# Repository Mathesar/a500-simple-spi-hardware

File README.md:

# a500-simple-spi-hardware
Simple SPI controller for the Amiga 500 with support for SD-cards and Ethernet controller. Tested on a rev. 5 Amiga 500. It might also work on other revisions and Amiga models but that has not been tested. The design is licensed under CERN OHL-S V2.0
This repository contains the hardware CAD files. For drivers look [here](https://github.com/Mathesar/a500-simple-spi-drivers).
This SPI controller is designed to be as simple as possible so that anyone can build it, hence the "simple" SPI controller.
The design uses no programmable logic chips but only jellybean 3.3V 74LVCXX logic chips and a jellybean quad analog switch.
To make it so simple compromises had to be made. The design therefore does not contain any shifting logic. This is a "bitbanging" design that can only receive or send 1 bit at a time. All the shifting is thus done by the driver software. It is not at bad as it seems though as the driver does not need to generate the SCLK signal.
The SCLK signal is generated automatically by the hardware whenever a bit is read or written. Therefore, using some optimised assembly, this controller can do about 60Kbytes/sec of raw throughput on a plain Amiga 500 with no FAST ram.

It seems I often need ~~3~~ 4 revisions to get things right :-). 

## Revision 1.0
Revision 1.0 was my first attempt. It used a 74HCT688 as the address decoder and did not set MOSI high on reads.
Therefore this version had problems with SD-cards. I fixed it by using A7 instead of D7 to write but this made writes very slow.
Also, the '688 is currently unobtainium. It seems that only simple logic chips like the '00 or '02 are available in all logic families.

## Revision 1.1
So, revision 1.1 was created that solved all above issues. This is the version you can see on the pictures. It no longer uses the 74HCT688 but a combination of OR, NOR and NAND gates.
However, even 1.1 had some minor issues. Firstly I made a small mistake in the address decoder. That one was very easy to patch though and after the patch everything functions as designed. Secondly however, the PCB was slightly too large at the top left corner causing the metal shield to no longer fit. (tested on a revision 5 Amiga 500)

## Revision 1.2
Therefore, revision 1.2 was created that fixes those final issues. I did not built it but it is basically revision 1.1 wwith a slightly resized PCB and the address decoder bug fixed. See [here](https://github.com/Mathesar/a500-simple-spi-hardware/tree/40606e6f381aa33d11fc7373534e6168bc126c18) for all the files for this rev 1.2.

**UPDATE 5-12-2022:**
The setup time on MOSI is marginal during reads. This is because of the ~DECODE signal feeding into U7A. To fix this, pin 2 of U7 should be lifted from the PCB so that it longer makes contact with the pad. This pin should then be connected to pin 3 of U7. On my system the hardware actually worked without the modification but some SD cards can get unreliable if this mod is not done

## Revision 1.3
This is the latest revision incorporating the MOSI setup fix. This version has been built and verified.

## Building hints:
This SPI controller is intended to give an Amiga 500 an SD-card (to be used as a harddisk) and ethernet connectivity. 
The ethernet module is optional and connected via a pinheader and some dupont jumper cables. The SD-card module is definately not optional and soldered directly to the interface as can be seen on the pictures. The reason for this is that the SD-card module supplies 3.3V to the logic chips (and to the optional ethernet controller) via it's onboard voltage regulator.
Pictures of the modules I used are in the schematic and in this repository. It is very important to use exactly the SD-card module as I used. 

The circuit depends on the pinout and the onboard voltage regulator. The circuit also contain an old-fashioned electrolytic capacitor on the +3.3V rail. This component is also mandatory! Without it the voltage regulator on the SD-card module might become unstable.
The pinheader for the SD-card actvity LED and the ethernet module should be right angle types or straight angle types bend over. Otherwise the whole setup becomes too high when the dupont cables are mounted. With right angle pins everything fits nicely under the metal shield.
The pinheader that connects the controller to the 68000 socket on the A500 main board should be "turned" types with round pins. The thin part plugs into the Amiga, the thicker part is soldered on the SPI controller. This is very important as the wrong pins might damage your 68000 socket.
The ethernet module does not really fit internally to the Amiga 500. I have used some long dupont cables that go through to the side expansion slot and the ethernet module is thus hanging outside. Maybe I build something like [this](https://www.thingiverse.com/thing:4830638) someday.

## HDD led
I hotglued a LED to the normal floppy LED and connected that to the LED pins on the simple SPI controller. A bit like done [here](https://www.youtube.com/watch?v=9V46ZEBu338) except that I used a single orange LED. Hotglue is easily removed with some IPA (isopropyl alcohol) if I ever change my mind. It looks really good:

## Compatiblity with other hardware
The simple SPI hardware uses a fixed address space in the upper region of the ZORRO-II IO space. Additional hardware like the A590 side-car should end up in the lower region of the ZORRO-II IO space so in theory they should not interfere. This is untested though.

A picture from the front of revision 1.1:

And a picture from the back of revision 1.1:

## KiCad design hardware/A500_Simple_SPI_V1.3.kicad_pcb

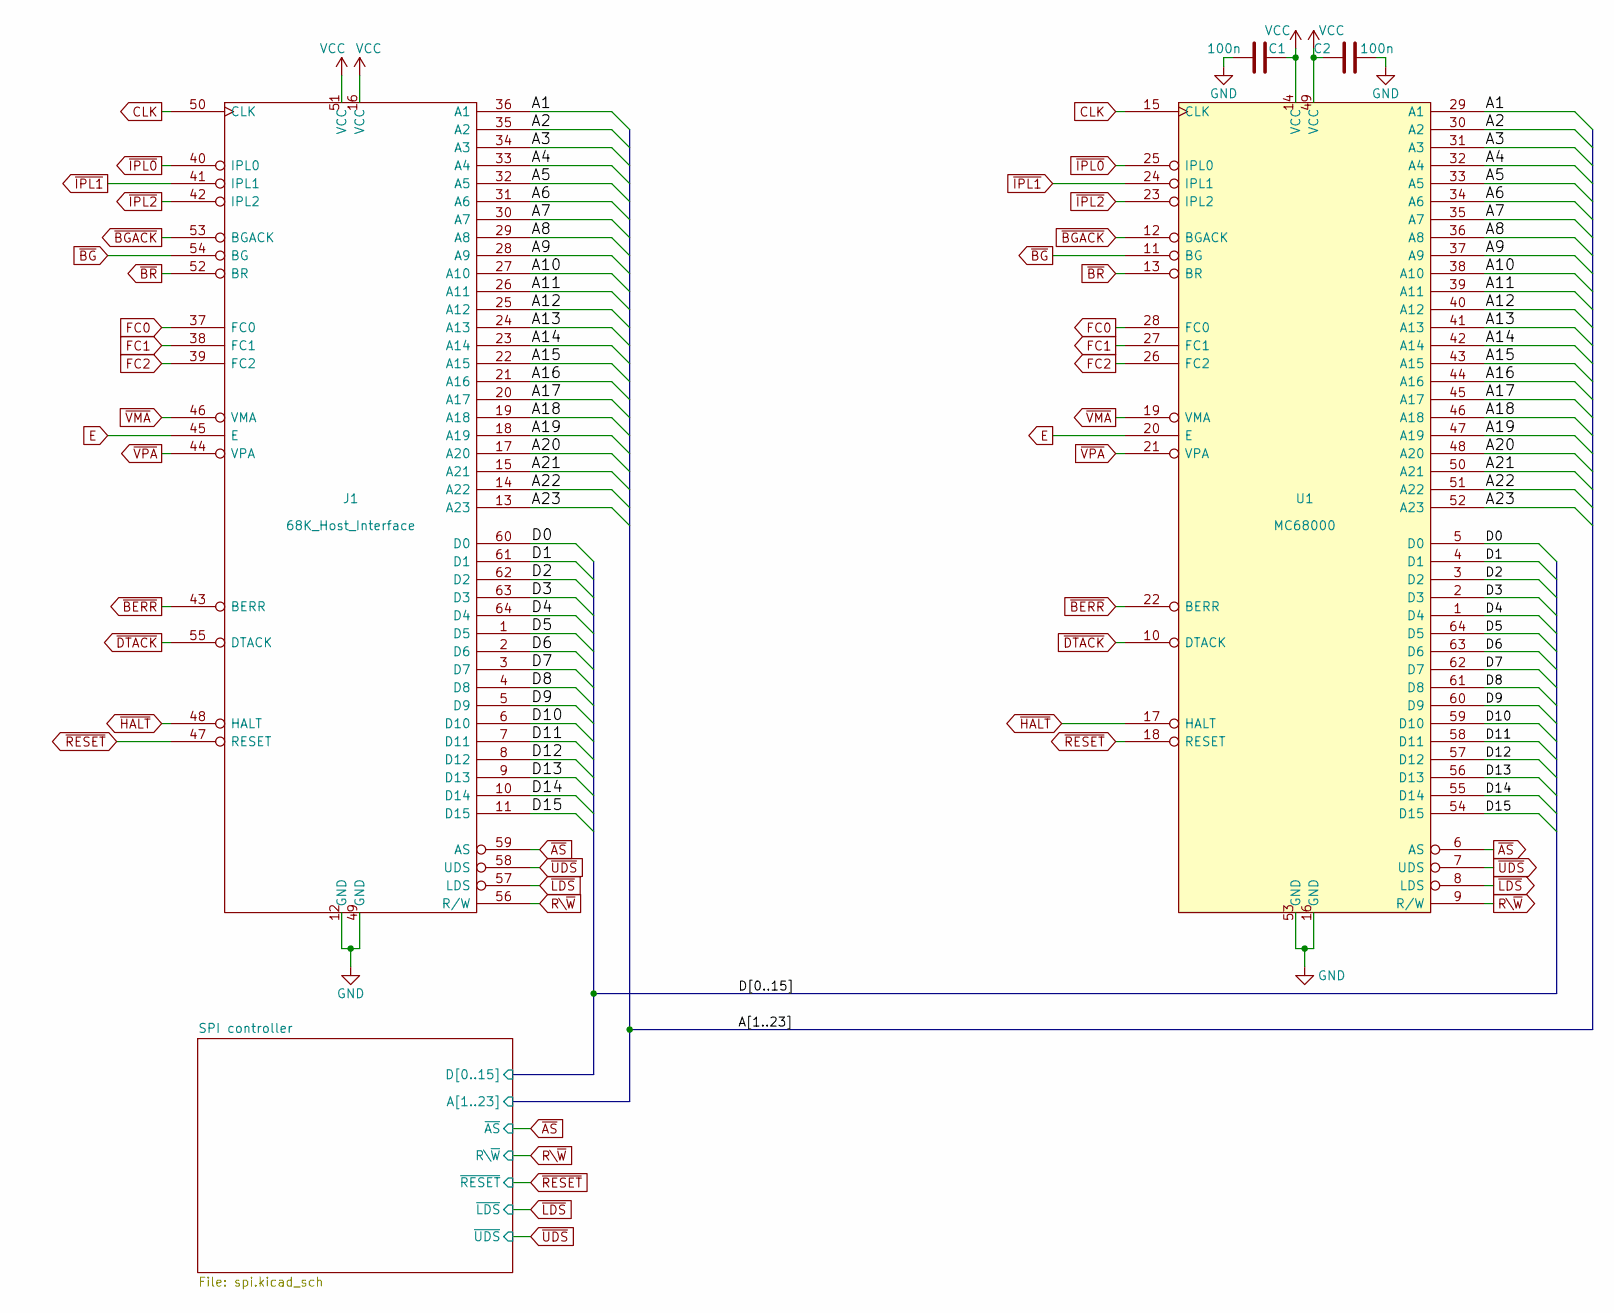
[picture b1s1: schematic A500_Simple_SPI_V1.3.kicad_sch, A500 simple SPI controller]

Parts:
C1, C2: 100n; C_0805_2012Metric_Pad1.18x1.45mm_HandSolder
J1: 68K_Host_Interface; DIP-64_W22.86mm_Socket
U1: MC68000; DIP-64_W22.86mm_Socket

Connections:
/A1: J1.36 (A1), U1.29 (A1)
/A2: J1.35 (A2), U1.30 (A2)
/A3: J1.34 (A3), U1.31 (A3)
/A4: J1.33 (A4), U1.32 (A4)
/A5: J1.32 (A5), U1.33 (A5)
/A6: J1.31 (A6), U1.34 (A6)
/A7: J1.30 (A7), U1.35 (A7)
/A8: J1.29 (A8), U1.36 (A8)
/A9: J1.28 (A9), U1.37 (A9)
/A10: J1.27 (A10), U1.38 (A10)
/A11: J1.26 (A11), U1.39 (A11)
/A12: J1.25 (A12), U1.40 (A12)
/A13: J1.24 (A13), U1.41 (A13)
/A14: J1.23 (A14), U1.42 (A14)
/A15: J1.22 (A15), U1.43 (A15)
/A16: J1.21 (A16), U1.44 (A16)
/A17: J1.20 (A17), U1.45 (A17)
/A18: J1.19 (A18), U1.46 (A18); also elsewhere on the board
/A19: J1.18 (A19), U1.47 (A19); also elsewhere on the board
/A20: J1.17 (A20), U1.48 (A20); also elsewhere on the board
/A21: J1.15 (A21), U1.50 (A21); also elsewhere on the board
/A22: J1.14 (A22), U1.51 (A22); also elsewhere on the board
/A23: J1.13 (A23), U1.52 (A23); also elsewhere on the board
/D0: J1.60 (D0), U1.5 (D0)
/D1: J1.61 (D1), U1.4 (D1)
/D2: J1.62 (D2), U1.3 (D2)
/D3: J1.63 (D3), U1.2 (D3)
/D4: J1.64 (D4), U1.1 (D4)
/D5: J1.1 (D5), U1.64 (D5)
/D6: J1.2 (D6), U1.63 (D6)
/D7: J1.3 (D7), U1.62 (D7); also elsewhere on the board
/D8: J1.4 (D8), U1.61 (D8); also elsewhere on the board
/D9: J1.5 (D9), U1.60 (D9); also elsewhere on the board
/D10: J1.6 (D10), U1.59 (D10)
/D11: J1.7 (D11), U1.58 (D11)
/D12: J1.8 (D12), U1.57 (D12)
/D13: J1.9 (D13), U1.56 (D13)
/D14: J1.10 (D14), U1.55 (D14)
/D15: J1.11 (D15), U1.54 (D15)
CLK: J1.50 (CLK), U1.15 (CLK)
E: J1.45 (E), U1.20 (E)
FC0: J1.37 (FC0), U1.28 (FC0)
FC1: J1.38 (FC1), U1.27 (FC1)
FC2: J1.39 (FC2), U1.26 (FC2)
GND: C1.1, C2.2, J1.12 (GND), J1.49 (GND), U1.16 (GND), U1.53 (GND); also elsewhere on the board
R\~W: J1.56 (R/W), U1.9 (R/W); also elsewhere on the board
VCC: C1.2, C2.1, J1.16 (VCC), J1.51 (VCC), U1.14 (VCC), U1.49 (VCC); also elsewhere on the board
~AS: J1.59 (AS), U1.6 (AS); also elsewhere on the board
~BERR: J1.43 (BERR), U1.22 (BERR)
~BGACK: J1.53 (BGACK), U1.12 (BGACK)
~BG: J1.54 (BG), U1.11 (BG)
~BR: J1.52 (BR), U1.13 (BR)
~DTACK: J1.55 (DTACK), U1.10 (DTACK)
~HALT: J1.48 (HALT), U1.17 (HALT)
~IPL0: J1.40 (IPL0), U1.25 (IPL0)
~IPL1: J1.41 (IPL1), U1.24 (IPL1)
~IPL2: J1.42 (IPL2), U1.23 (IPL2)
~LDS: J1.57 (LDS), U1.8 (LDS); also elsewhere on the board
~RESET: J1.47 (RESET), U1.18 (RESET); also elsewhere on the board
~UDS: J1.58 (UDS), U1.7 (UDS); also elsewhere on the board
~VMA: J1.46 (VMA), U1.19 (VMA)
~VPA: J1.44 (VPA), U1.21 (VPA)

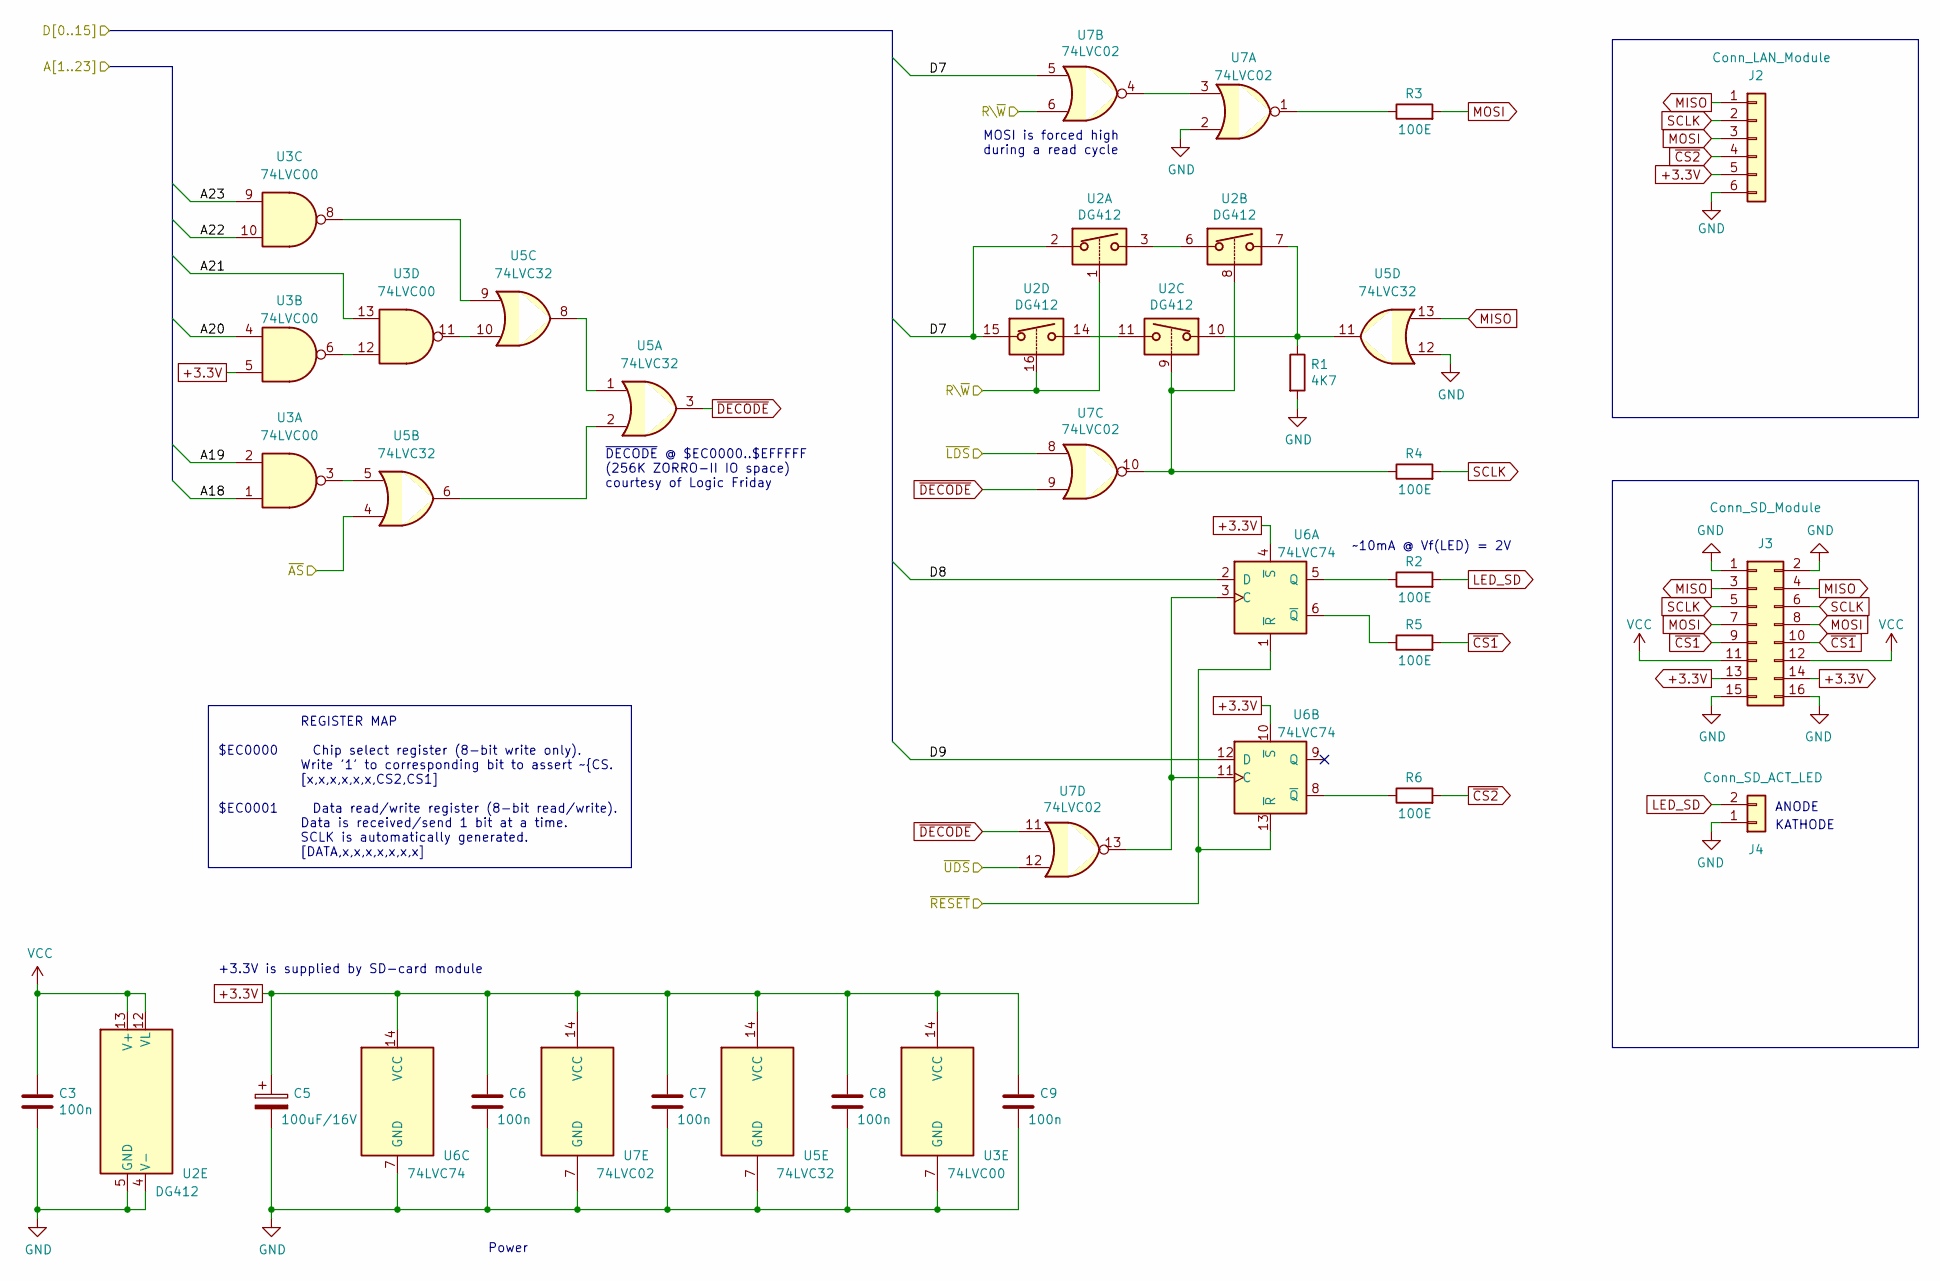
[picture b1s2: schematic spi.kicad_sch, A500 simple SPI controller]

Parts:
C3, C6, C7, C8, C9: 100n; C_0805_2012Metric_Pad1.18x1.45mm_HandSolder
C5: 100uF/16V; C_Radial_D5.0mm_H7.0mm_P2.00mm
J2: Conn_LAN_Module; PinHeader_1x06_P2.54mm_Vertical
J3: Conn_SD_Module; PinHeader_2x08_P2.54mm_Vertical
J4: Conn_SD_ACT_LED; PinHeader_1x02_P2.54mm_Vertical
R1: 4K7; R_0805_2012Metric_Pad1.20x1.40mm_HandSolder
R2, R3, R4, R5, R6: 100E; R_0805_2012Metric_Pad1.20x1.40mm_HandSolder
U2: DG412; SOIC-16_3.9x9.9mm_P1.27mm
U3: 74LVC00; SOIC-14_3.9x8.7mm_P1.27mm
U5: 74LVC32; SOIC-14_3.9x8.7mm_P1.27mm
U6: 74LVC74; SOIC-14_3.9x8.7mm_P1.27mm
U7: 74LVC02; SOIC-14_3.9x8.7mm_P1.27mm

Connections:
+3.3V: C5.1, C6.1, C7.1, C8.1, C9.1, J2.5, J3.13, J3.14, U3.5, U3.14 (VCC), U5.14 (VCC), U6.4 (~S), U6.10 (~S), U6.14 (VCC), U7.14 (VCC)
/A18: U3.1; also elsewhere on the board
/A19: U3.2; also elsewhere on the board
/A20: U3.4; also elsewhere on the board
/A21: U3.13; also elsewhere on the board
/A22: U3.10; also elsewhere on the board
/A23: U3.9; also elsewhere on the board
/D7: U2.2, U2.15, U7.5; also elsewhere on the board
/D8: U6.2 (D); also elsewhere on the board
/D9: U6.12 (D); also elsewhere on the board
GND: C3.2, C5.2, C6.2, C7.2, C8.2, C9.2, J2.6, J3.1, J3.2, J3.15, J3.16, J4.1, R1.2, U2.4 (V-), U2.5 (GND), U3.7 (GND), U5.7 (GND), U5.12, U6.7 (GND), U7.2, U7.7 (GND); also elsewhere on the board
LED_SD: J4.2, R2.2
MISO: J2.1, J3.3, J3.4, U5.13
MOSI: J2.3, J3.7, J3.8, R3.2
unnamed: R1.1, U2.7, U2.10, U5.11
unnamed: R2.1, U6.5 (Q)
unnamed: R3.1, U7.1
unnamed: R4.1, U2.8, U2.9, U7.10
unnamed: R5.1, U6.6 (~Q)
unnamed: R6.1, U6.8 (~Q)
unnamed: U2.3, U2.6
unnamed: U2.11, U2.14
unnamed: U3.3, U5.5
unnamed: U3.8, U5.9
unnamed: U3.11, U5.10
unnamed: U3.6, U3.12
unnamed: U5.1, U5.8
unnamed: U5.2, U5.6
unnamed: U6.3 (C), U6.11 (C), U7.13
unnamed: U7.3, U7.4
R\~W: U2.1, U2.16, U7.6; also elsewhere on the board
SCLK: J2.2, J3.5, J3.6, R4.2
VCC: C3.1, J3.11, J3.12, U2.12 (VL), U2.13 (V+); also elsewhere on the board
~AS: U5.4; also elsewhere on the board
~CS1: J3.9, J3.10, R5.2
~CS2: J2.4, R6.2
~DECODE: U5.3, U7.9, U7.11
~LDS: U7.8; also elsewhere on the board
~RESET: U6.1 (~R), U6.13 (~R); also elsewhere on the board
~UDS: U7.12; also elsewhere on the board

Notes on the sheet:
REGISTER MAP $EC0000 Chip select register (8-bit write only). Write '1' to corresponding bit to assert ~{CS. [x,x,x,x,x,x,CS2,CS1] $EC0001 Data read/write register (8-bit read/write). Data is received/send 1 bit at a time. SCLK is automatically generated. [DATA,x,x,x,x,x,x,x]
~{DECODE} @ $EC0000..$EFFFFF (256K ZORRO-II IO space) courtesy of Logic Friday
+3.3V is supplied by SD-card module
Power
~10mA @ Vf(LED) = 2V
KATHODE
MOSI is forced high during a read cycle
ANODE

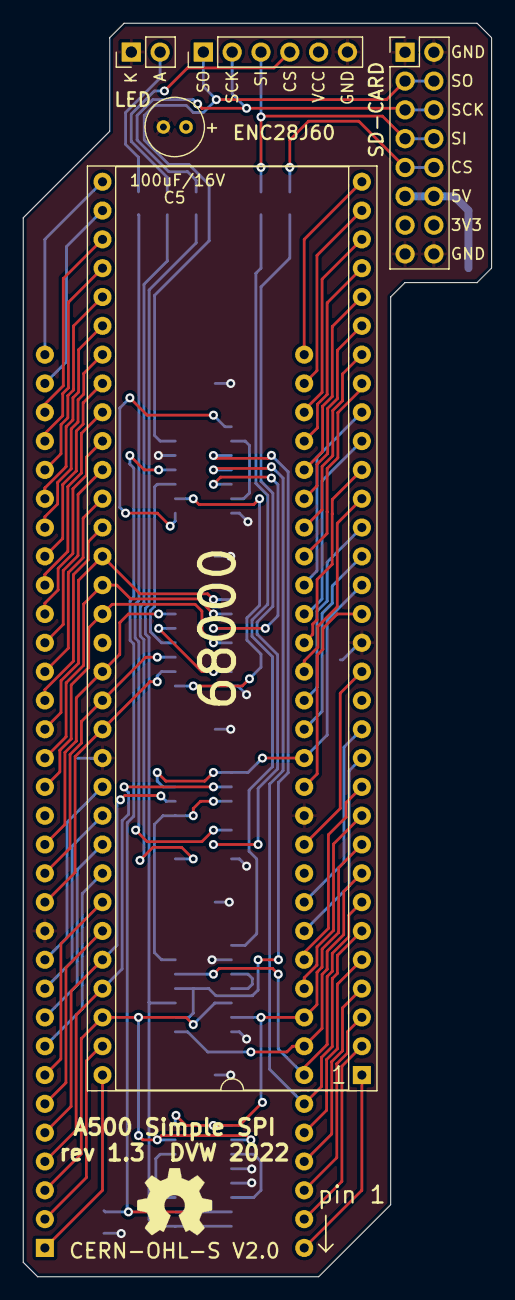
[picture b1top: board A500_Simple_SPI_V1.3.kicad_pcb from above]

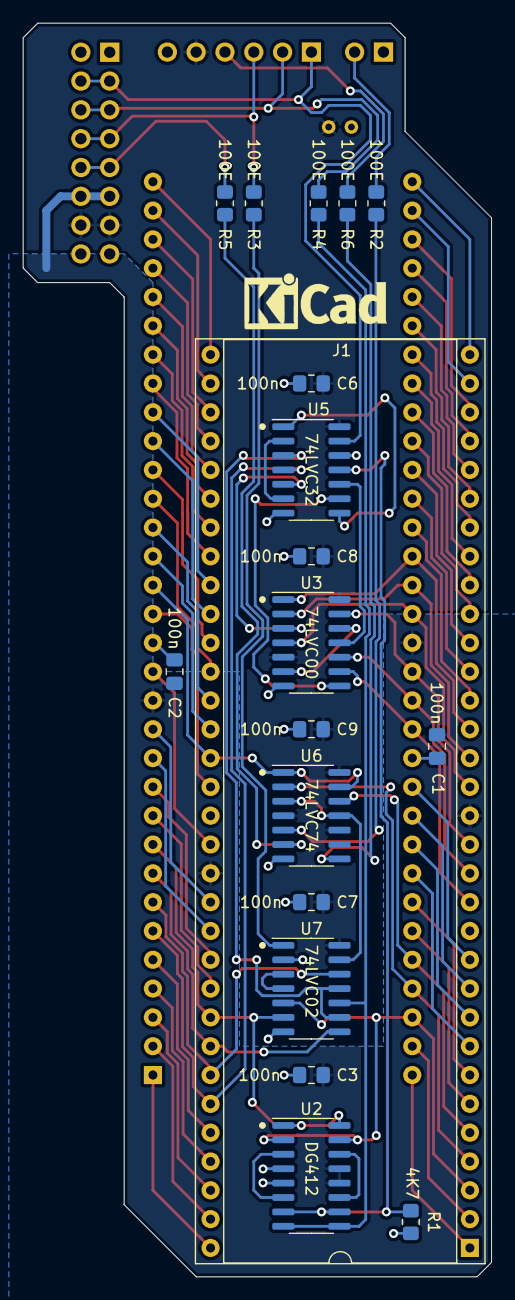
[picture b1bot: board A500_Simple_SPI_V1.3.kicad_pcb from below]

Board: 2 copper layers, 41.3 x 110.5 mm, 24 parts (19 on the bottom side), 86 nets.

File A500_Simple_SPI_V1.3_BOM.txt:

"Designator"			"Quantity"		"Description"
"J4"				1			2pins 2.54mm male pin header for SD activity LED	
"C5"				1			100uF/16V 2mm pitch electrolytic, NO low ESR type!!!
"J3"				1			SD-card module, see pictures
"U1"				1			64pin DIL socket for 68000 processor
"J2"				1			6pins 2.54mm male pin header for optional ENC28J60 module
"R3,R6,R5,R4,R2"		5			100E 0805 resistor
"U2"				1			DG412 SOIC
"C2,C9,C1,C7,C3,C6,C8";		7			100n 0805 X7R/X5R capacitor
"R1"				1			4K7 0805 resistor
"U6"				1			74LVC74	SOIC
"U7"				1			74LVC02	SOIC
"U3"				1			74LVC00	SOIC
"U5"				1			74LVC32	SOIC
"J1"				1			64pin or 2*32pin ROUND pinheader for connecting to A500 main board

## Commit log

2022-11-17 first commit
    no BOM yet
    no gerbers yet
2022-11-18 Added pictures of ethernet and SD-card modules
2022-11-18 render of revision 1.2
2022-11-18 more pictures
2022-11-18 added hdd benchmark
2022-11-21 Added bill of materials
2022-12-05 Added info on MOSI setup mod to schematics
2022-12-05 Updated readme with MOSI setup fix
2022-12-06 New Revision 1.3 which improves MOSI setup times on reads
2022-12-06 Delete A500_Simple_SPI_V1.2.jpg
    Obsolote version
2022-12-06 New version 1.3 render
2022-12-27 new pictures of rev 1.3
